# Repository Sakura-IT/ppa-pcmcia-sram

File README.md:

ppa-pcmcia-sram
===============

PCMCIA SRAM card created on ppa.pl forum.

* board - electrical schematics and board layout (Eagle, Gerber)
* cpld/src - CPLD core source (VHDL)
* docs - documentation (manual)

For history and rationale behind design decisions, See this thread: http://www.ppa.pl/forum/amiga/29264/budowa-kart-pamieci-sram-na-pcmcia

This board was sold and marketed as Sakura 4MB PCMCIA SRAM, primarily by Sakura IT, though several forks of this design exist.

Description
===========

Add 4MB of Fast RAM to your unexpanded Amiga 600/1200. This additional memory will make your system much faster and allow to run more demanding games and applications. It was designed by Jarosław Bieliński and Radosław Kujawa.

This memory expansion card has the following features:

* Adds 4MB of Fast RAM to Amiga 600 or Amiga 1200.
* Built using modern, high performance 55ns SRAM ICs (even faster than maximum Amiga 1200 slot access time).
* Accelerates unexpanded Amiga 1200 to at least 1.67 MIPS (according to SysInfo).
* Fully PCMCIA 2.1 compliant on an electrical level, smaller dimensions than normal PCMCIA card.
* Very simple installation - just insert the card into PCMCIA slot on the left side of Amiga.
* Compatible with all PCMCIA friendly accelerators and memory expansions.
* Open source design. 
* RoHS compliant, low power, environmentally friendly.
* Made by Amigans for Amigans!

We did our best to ensure that this card works on as many configurations as possible, but some accelerator and Fast RAM expansion designs are inherently incompatible with PCMCIA slot if more than 4MB of memory is installed. Note that PCMCIA SRAM should work with them anyway, if less than 4MB Fast was installed on the turbo card. Of course, if you don’t have any accelerator, you don’t have to worry about that.

The following A1200 cards are known to be PCMCIA compatible and should work correctly with any amount of memory installed:

* Blizzard 1230/1240/1260.
* Apollo 1240/1260.
* ACA 1220/1230/1231/1232.
* most other turbo cards supporting more than 8MB of Fast memory.
* 4MB Fast trapdoor expansions without CPU.

The following A1200 cards are known to be problematic if more than 4MB of memory is installed:

* Apollo/Elbox/Viper 1230LC.
* M-Tec 1230/28.
* Blizzard 1220 if more than 4MB RAM installed.
* 8MB Fast trapdoor expansions without CPU.

The following A600 cards are known to be PCMCIA compatible and should work correctly:

* ACA630.
* 4MB Fast expansions attached on top of processor.

The following A600 cards are known to be problematic if more than 4MB of memory is installed:

* ACA620 (in default PCMCIA-incompatible mode).
* Ninetails (in default PCMCIA-incompatible mode).
* 8MB/9.5MB Fast expansions attached on top of processor.

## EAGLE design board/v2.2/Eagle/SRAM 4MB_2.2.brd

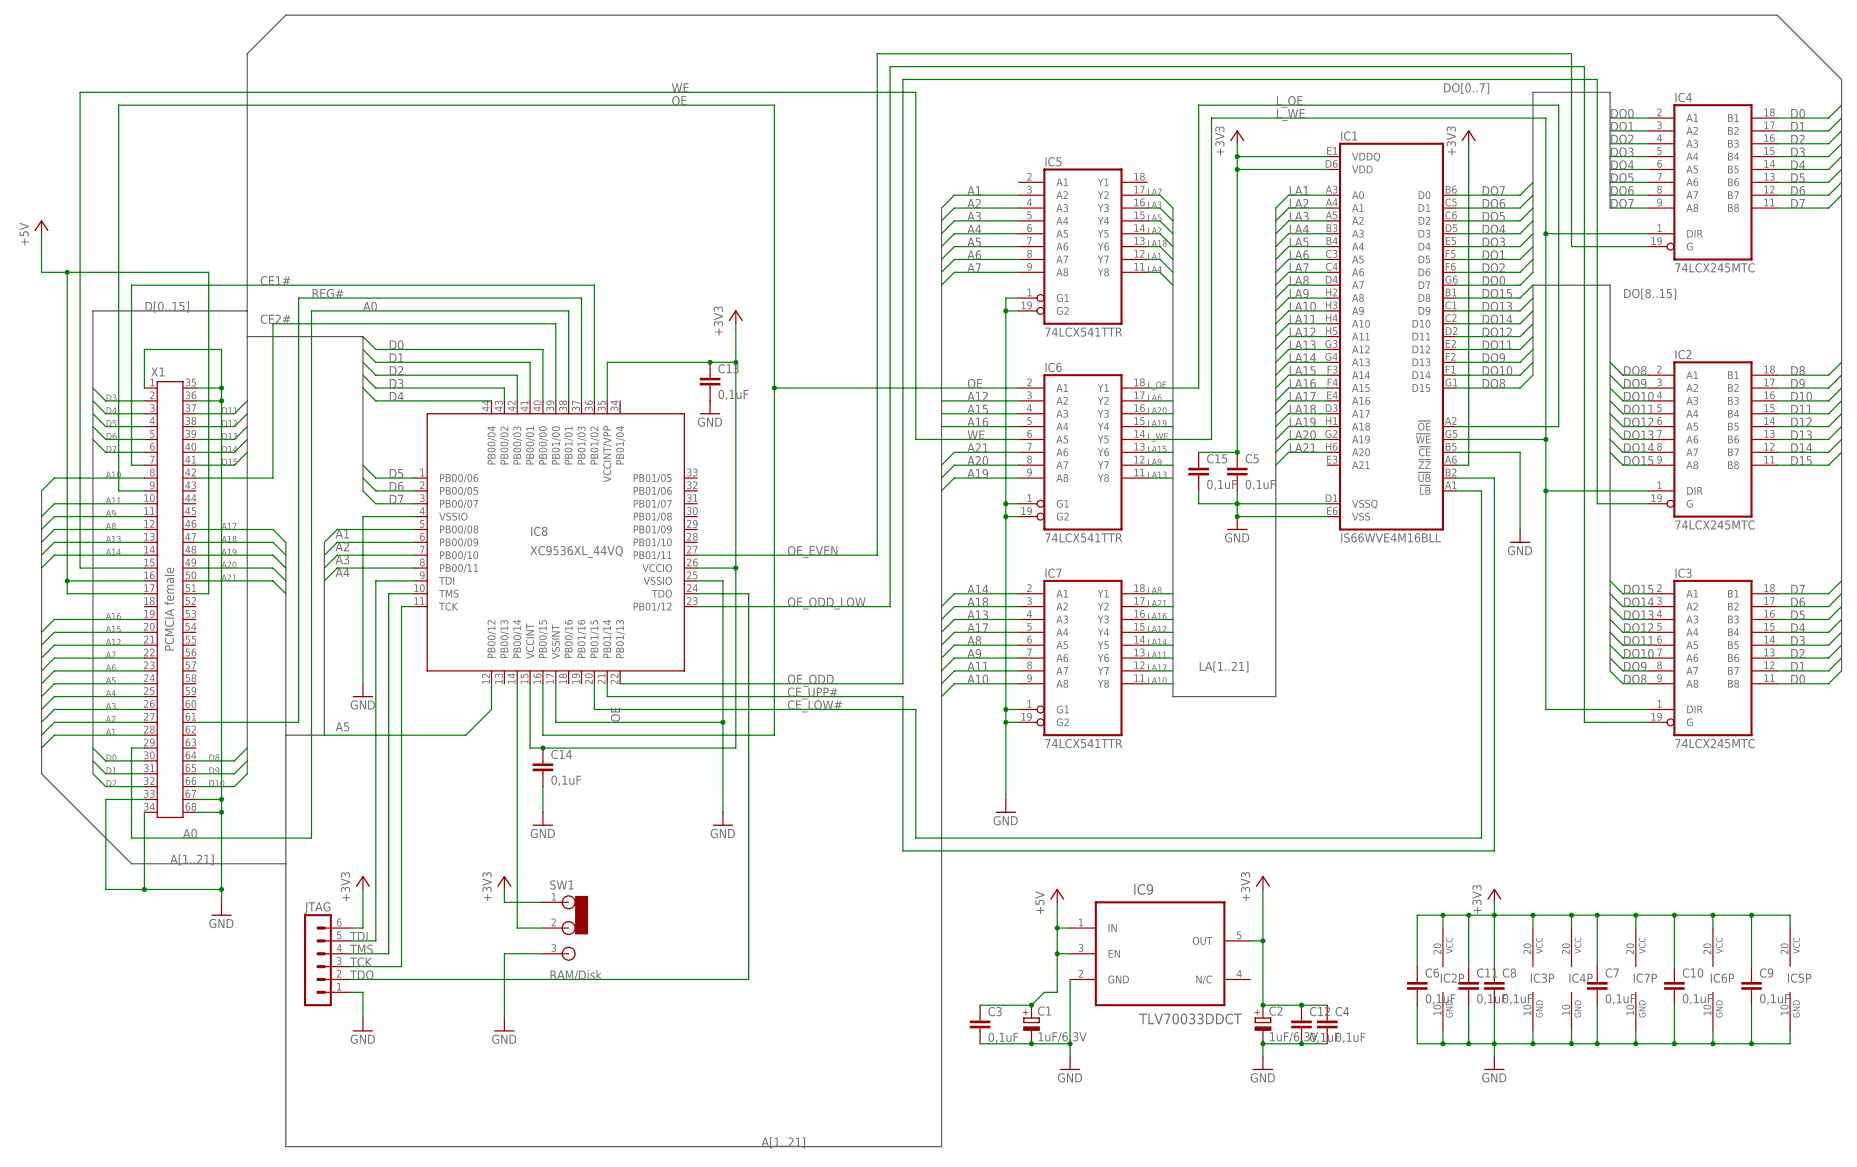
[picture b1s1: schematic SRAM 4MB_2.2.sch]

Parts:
C1, C2: 1uF/6,3V; A/3216-18R
C3, C4: 0,1uF; C0603
C5, C6, C7, C8, C9, C10, C11, C12, C13, C14, C15: 0,1uF; C0402K
IC1: IS66WVE4M16BLL; TFBGA48
IC2, IC3, IC4: 74LCX245MTC; TSSOP20
IC5, IC6, IC7: 74LCX541TTR; TSSOP20
IC8: XC9536XL_44VQ; SQFP-S-10X10-44
IC9: TLV70033DDCT; SOT95P280X110-5N
JTAG: MA06-1
SW1: RAM/Disk; SWITCH2
X1: PCMCIA female; 9M681X04

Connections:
+3V3: C2.+, C4.1, C5.1, C6.1, C7.1, C8.1, C9.1, C10.1, C11.1, C12.1, C13.1, C14.1, C15.1, IC1.A6 (!ZZ), IC1.D6 (VDD), IC1.E1 (VDDQ), IC2.20 (VCC), IC3.20 (VCC), IC4.20 (VCC), IC5.20 (VCC), IC6.20 (VCC), IC7.20 (VCC), IC8.15 (VCCINT), IC8.26 (VCCIO), IC8.35 (VCCINT/VPP), IC9.5 (OUT), JTAG.6, SW1.1
+5V: C1.+, C3.1, IC9.1 (IN), IC9.3 (EN), X1.16, X1.17, X1.51
A0: IC8.38 (PB01/01), X1.29
A1: IC5.3 (A2), IC8.5 (PB00/08), X1.28
A2: IC5.4 (A3), IC8.6 (PB00/09), X1.27
A3: IC5.5 (A4), IC8.7 (PB00/10), X1.26
A4: IC5.6 (A5), IC8.8 (PB00/11), X1.25
A5: IC5.7 (A6), IC8.12 (PB00/12), X1.24
A6: IC5.8 (A7), X1.23
A7: IC5.9 (A8), X1.22
A8: IC7.6 (A5), X1.12
A9: IC7.7 (A6), X1.11
A10: IC7.9 (A8), X1.8
A11: IC7.8 (A7), X1.10
A12: IC6.3 (A2), X1.21
A13: IC7.4 (A3), X1.13
A14: IC7.2 (A1), X1.14
A15: IC6.4 (A3), X1.20
A16: IC6.5 (A4), X1.19
A17: IC7.5 (A4), X1.46
A18: IC7.3 (A2), X1.47
A19: IC6.9 (A8), X1.48
A20: IC6.8 (A7), X1.49
A21: IC6.7 (A6), X1.50
CE1#: IC8.36 (PB01/02), X1.7
CE2#: IC8.39 (PB01/00), X1.42
CE_LOW#: IC1.A1 (!LB), IC8.20 (PB01/15)
CE_UPP#: IC1.B2 (!UB), IC8.21 (PB01/14)
D0: IC3.11 (B8), IC4.18 (B1), IC8.40 (PB00/00), X1.30
D1: IC3.12 (B7), IC4.17 (B2), IC8.41 (PB00/01), X1.31
D2: IC3.13 (B6), IC4.16 (B3), IC8.42 (PB00/03), X1.32
D3: IC3.14 (B5), IC4.15 (B4), IC8.43 (PB00/02), X1.2
D4: IC3.15 (B4), IC4.14 (B5), IC8.44 (PB00/04), X1.3
D5: IC3.16 (B3), IC4.13 (B6), IC8.1 (PB00/06), X1.4
D6: IC3.17 (B2), IC4.12 (B7), IC8.2 (PB00/05), X1.5
D7: IC3.18 (B1), IC4.11 (B8), IC8.3 (PB00/07), X1.6
D8: IC2.18 (B1), X1.64
D9: IC2.17 (B2), X1.65
D10: IC2.16 (B3), X1.66
D11: IC2.15 (B4), X1.37
D12: IC2.14 (B5), X1.38
D13: IC2.13 (B6), X1.39
D14: IC2.12 (B7), X1.40
D15: IC2.11 (B8), X1.41
DO0: IC1.G6 (D7), IC4.2 (A1)
DO1: IC1.F5 (D5), IC4.3 (A2)
DO2: IC1.F6 (D6), IC4.4 (A3)
DO3: IC1.E5 (D4), IC4.5 (A4)
DO4: IC1.D5 (D3), IC4.6 (A5)
DO5: IC1.C6 (D2), IC4.7 (A6)
DO6: IC1.C5 (D1), IC4.8 (A7)
DO7: IC1.B6 (D0), IC4.9 (A8)
DO8: IC1.G1 (D15), IC2.2 (A1), IC3.9 (A8)
DO9: IC1.F2 (D13), IC2.3 (A2), IC3.8 (A7)
DO10: IC1.F1 (D14), IC2.4 (A3), IC3.7 (A6)
DO11: IC1.E2 (D12), IC2.5 (A4), IC3.6 (A5)
DO12: IC1.D2 (D11), IC2.6 (A5), IC3.5 (A4)
DO13: IC1.C1 (D9), IC2.7 (A6), IC3.4 (A3)
DO14: IC1.C2 (D10), IC2.8 (A7), IC3.3 (A2)
DO15: IC1.B1 (D8), IC2.9 (A8), IC3.2 (A1)
GND: C1.-, C2.-, C3.2, C4.2, C5.2, C6.2, C7.2, C8.2, C9.2, C10.2, C11.2, C12.2, C13.2, C14.2, C15.2, IC1.B5 (!CE), IC1.D1 (VSSQ), IC1.E6 (VSS), IC2.10 (GND), IC3.10 (GND), IC4.10 (GND), IC5.1 (G1), IC5.10 (GND), IC5.19 (G2), IC6.1 (G1), IC6.10 (GND), IC6.19 (G2), IC7.1 (G1), IC7.10 (GND), IC7.19 (G2), IC8.4 (VSSIO), IC8.17 (VSSINT), IC8.25 (VSSIO), IC9.2 (GND), JTAG.1, SW1.3, X1.1, X1.33, X1.34, X1.35, X1.36, X1.67, X1.68
LA1: IC1.A3 (A0), IC5.12 (Y7)
LA2: IC1.A4 (A1), IC5.14 (Y5)
LA3: IC1.A5 (A2), IC5.16 (Y3)
LA4: IC1.B3 (A3), IC5.11 (Y8)
LA5: IC1.B4 (A4), IC5.15 (Y4)
LA6: IC1.C3 (A5), IC6.17 (Y2)
LA7: IC1.C4 (A6), IC5.17 (Y2)
LA8: IC1.D4 (A7), IC7.18 (Y1)
LA9: IC1.H2 (A8), IC6.12 (Y7)
LA10: IC1.H3 (A9), IC7.11 (Y8)
LA11: IC1.H4 (A10), IC7.13 (Y6)
LA12: IC1.H5 (A11), IC7.15 (Y4)
LA13: IC1.G3 (A12), IC6.11 (Y8)
LA14: IC1.G4 (A13), IC7.14 (Y5)
LA15: IC1.F3 (A14), IC6.13 (Y6)
LA16: IC1.F4 (A15), IC7.16 (Y3)
LA17: IC1.E4 (A16), IC7.12 (Y7)
LA18: IC1.D3 (A17), IC5.13 (Y6)
LA19: IC1.H1 (A18), IC6.15 (Y4)
LA20: IC1.G2 (A19), IC6.16 (Y3)
LA21: IC1.H6 (A20), IC7.17 (Y2)
L_OE: IC1.A2 (!OE), IC6.18 (Y1)
L_WE: IC1.G5 (!WE), IC2.1 (DIR), IC3.1 (DIR), IC4.1 (DIR), IC6.14 (Y5)
unnamed: IC8.14 (PB00/14), SW1.2
OE: IC6.2 (A1), IC8.16 (PB00/15), X1.9
OE_EVEN: IC4.19 (G), IC8.27 (PB01/11)
OE_ODD: IC2.19 (G), IC8.22 (PB01/13)
OE_ODD_LOW: IC3.19 (G), IC8.23 (PB01/12)
REG#: IC8.37 (PB01/03), X1.61
TCK: IC8.11 (TCK), JTAG.3
TDI: IC8.9 (TDI), JTAG.5
TDO: IC8.24 (TDO), JTAG.2
TMS: IC8.10 (TMS), JTAG.4
WE: IC6.6 (A5), X1.15

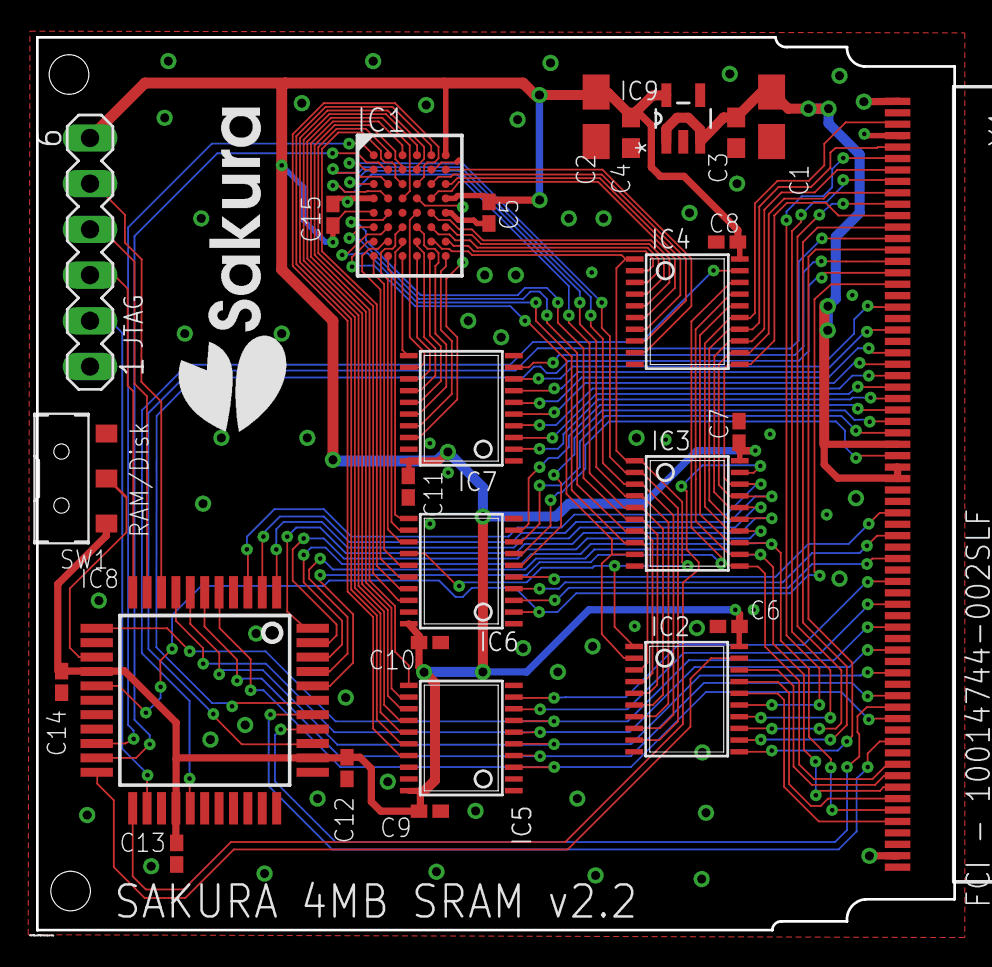
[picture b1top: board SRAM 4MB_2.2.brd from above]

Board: 2 copper layers, 51.0 x 49.6 mm, 27 parts (0 on the bottom side), 95 nets.

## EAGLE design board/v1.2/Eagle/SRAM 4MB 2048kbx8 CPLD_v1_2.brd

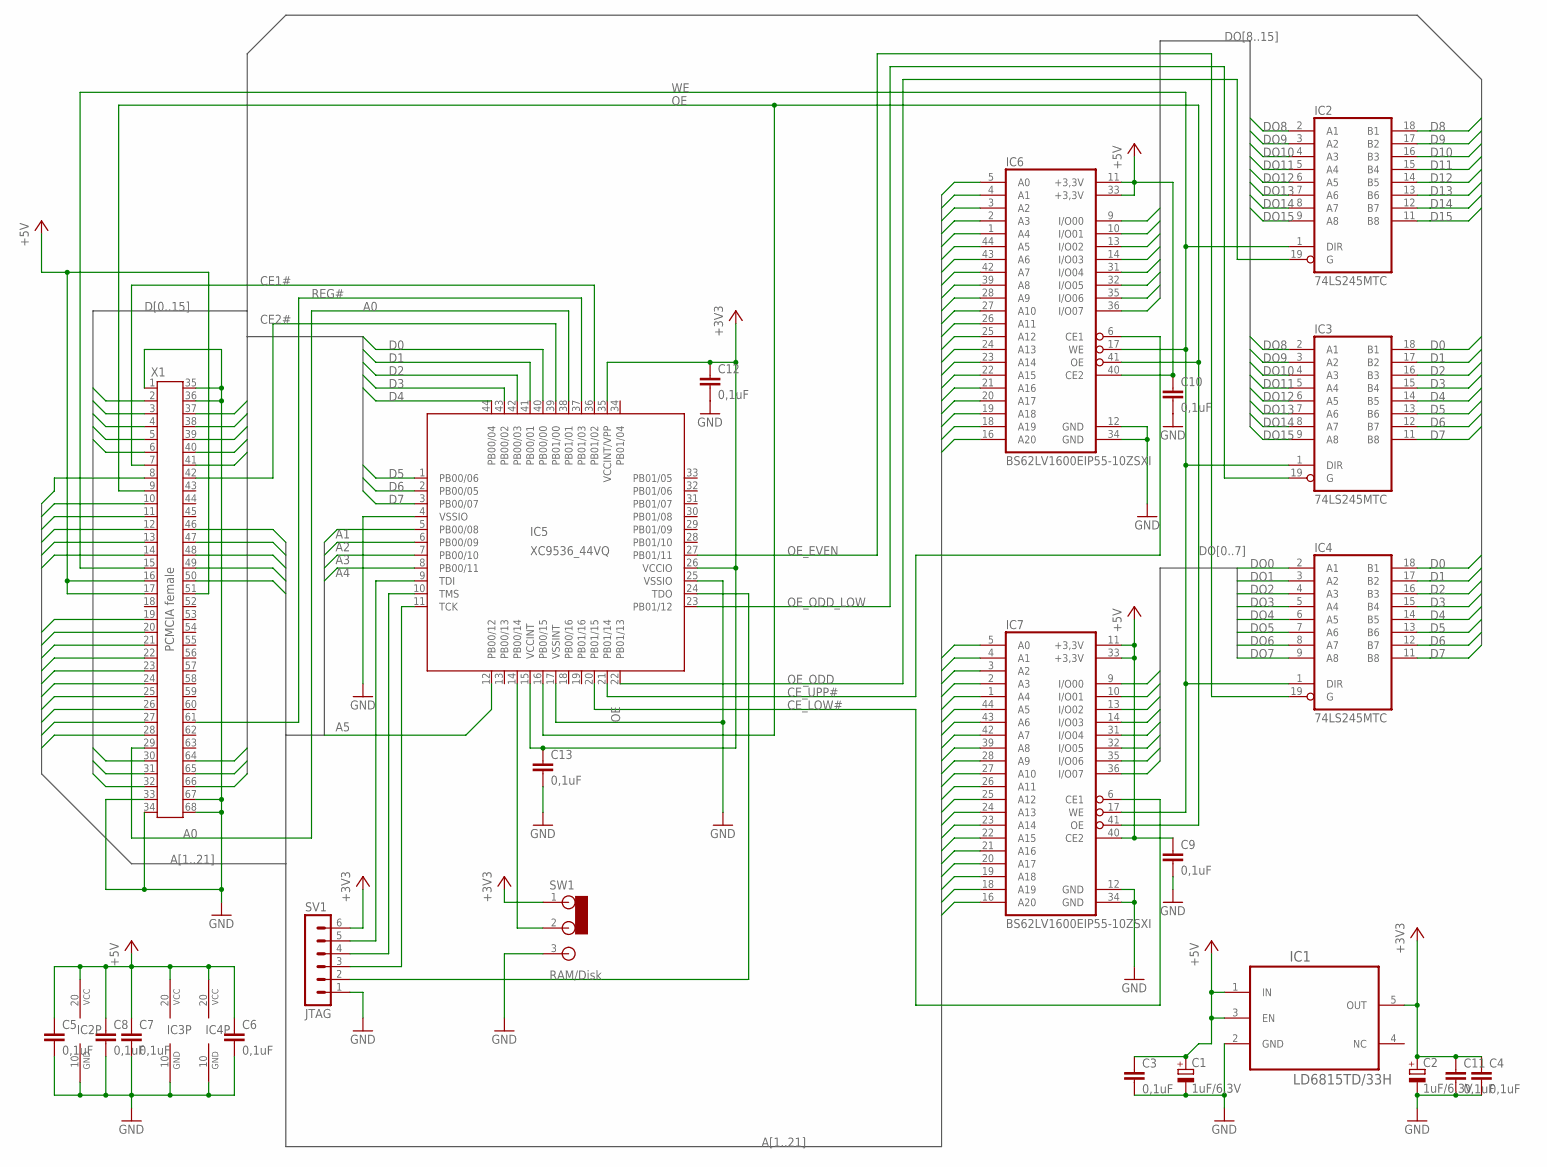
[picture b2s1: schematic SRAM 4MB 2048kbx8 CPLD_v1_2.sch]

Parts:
C1, C2: 1uF/6,3V; A/3216-18R
C3, C4, C5, C6, C7, C8, C9, C10, C11, C12, C13: 0,1uF; C0603
IC1: LD6815TD/33H; SOT95P275X110-5N
IC2, IC3, IC4: 74LS245MTC; TSSOP20
IC5: XC9536_44VQ; SQFP-S-10X10-44
IC6, IC7: BS62LV1600EIP55-10ZSXI; TSOPII-Z44
SV1: JTAG; MA06-1
SW1: RAM/Disk; SWITCH2
X1: PCMCIA female; 9M681X04

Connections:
+3V3: C2.+, C4.1, C11.1, C12.1, C13.1, IC1.5 (OUT), IC5.15 (VCCINT), IC5.26 (VCCIO), IC5.35 (VCCINT/VPP), SV1.6, SW1.1
+5V: C1.+, C3.1, C5.1, C6.1, C7.1, C8.1, C9.1, C10.1, IC1.1 (IN), IC1.3 (EN), IC2.20 (VCC), IC3.20 (VCC), IC4.20 (VCC), IC6.11 (+3,3V), IC6.33 (+3,3V), IC6.40 (CE2), IC7.11 (+3,3V), IC7.33 (+3,3V), IC7.40 (CE2), X1.16, X1.17, X1.51
A0: IC5.38 (PB01/01), X1.29
A1: IC5.5 (PB00/08), IC6.5 (A0), IC7.5 (A0), X1.28
A2: IC5.6 (PB00/09), IC6.4 (A1), IC7.4 (A1), X1.27
A3: IC5.7 (PB00/10), IC6.3 (A2), IC7.3 (A2), X1.26
A4: IC5.8 (PB00/11), IC6.2 (A3), IC7.2 (A3), X1.25
A5: IC5.12 (PB00/12), IC6.1 (A4), IC7.1 (A4), X1.24
A6: IC6.44 (A5), IC7.44 (A5), X1.23
A7: IC6.43 (A6), IC7.43 (A6), X1.22
A8: IC6.42 (A7), IC7.42 (A7), X1.12
A9: IC6.39 (A8), IC7.39 (A8), X1.11
A10: IC6.28 (A9), IC7.28 (A9), X1.8
A11: IC6.27 (A10), IC7.27 (A10), X1.10
A12: IC6.26 (A11), IC7.26 (A11), X1.21
A13: IC6.25 (A12), IC7.25 (A12), X1.13
A14: IC6.24 (A13), IC7.24 (A13), X1.14
A15: IC6.23 (A14), IC7.23 (A14), X1.20
A16: IC6.22 (A15), IC7.22 (A15), X1.19
A17: IC6.21 (A16), IC7.21 (A16), X1.46
A18: IC6.20 (A17), IC7.20 (A17), X1.47
A19: IC6.19 (A18), IC7.19 (A18), X1.48
A20: IC6.18 (A19), IC7.18 (A19), X1.49
A21: IC6.16 (A20), IC7.16 (A20), X1.50
CE1#: IC5.36 (PB01/02), X1.7
CE2#: IC5.39 (PB01/00), X1.42
CE_LOW#: IC5.20 (PB01/15), IC7.6 (CE1)
CE_UPP#: IC5.21 (PB01/14), IC6.6 (CE1)
D0: IC3.18 (B1), IC4.18 (B1), IC5.40 (PB00/00), X1.30
D1: IC3.17 (B2), IC4.17 (B2), IC5.41 (PB00/01), X1.31
D2: IC3.16 (B3), IC4.16 (B3), IC5.42 (PB00/03), X1.32
D3: IC3.15 (B4), IC4.15 (B4), IC5.43 (PB00/02), X1.2
D4: IC3.14 (B5), IC4.14 (B5), IC5.44 (PB00/04), X1.3
D5: IC3.13 (B6), IC4.13 (B6), IC5.1 (PB00/06), X1.4
D6: IC3.12 (B7), IC4.12 (B7), IC5.2 (PB00/05), X1.5
D7: IC3.11 (B8), IC4.11 (B8), IC5.3 (PB00/07), X1.6
D8: IC2.18 (B1), X1.64
D9: IC2.17 (B2), X1.65
D10: IC2.16 (B3), X1.66
D11: IC2.15 (B4), X1.37
D12: IC2.14 (B5), X1.38
D13: IC2.13 (B6), X1.39
D14: IC2.12 (B7), X1.40
D15: IC2.11 (B8), X1.41
DO0: IC4.2 (A1), IC7.9 (I/O00)
DO1: IC4.3 (A2), IC7.10 (I/O01)
DO2: IC4.4 (A3), IC7.13 (I/O02)
DO3: IC4.5 (A4), IC7.14 (I/O03)
DO4: IC4.6 (A5), IC7.31 (I/O04)
DO5: IC4.7 (A6), IC7.32 (I/O05)
DO6: IC4.8 (A7), IC7.35 (I/O06)
DO7: IC4.9 (A8), IC7.36 (I/O07)
DO8: IC2.2 (A1), IC3.2 (A1), IC6.9 (I/O00)
DO9: IC2.3 (A2), IC3.3 (A2), IC6.10 (I/O01)
DO10: IC2.4 (A3), IC3.4 (A3), IC6.13 (I/O02)
DO11: IC2.5 (A4), IC3.5 (A4), IC6.14 (I/O03)
DO12: IC2.6 (A5), IC3.6 (A5), IC6.31 (I/O04)
DO13: IC2.7 (A6), IC3.7 (A6), IC6.32 (I/O05)
DO14: IC2.8 (A7), IC3.8 (A7), IC6.35 (I/O06)
DO15: IC2.9 (A8), IC3.9 (A8), IC6.36 (I/O07)
GND: C1.-, C2.-, C3.2, C4.2, C5.2, C6.2, C7.2, C8.2, C9.2, C10.2, C11.2, C12.2, C13.2, IC1.2 (GND), IC2.10 (GND), IC3.10 (GND), IC4.10 (GND), IC5.4 (VSSIO), IC5.17 (VSSINT), IC5.25 (VSSIO), IC6.12 (GND), IC6.34 (GND), IC7.12 (GND), IC7.34 (GND), SV1.1, SW1.3, X1.1, X1.33, X1.34, X1.35, X1.36, X1.67, X1.68
unnamed: IC5.24 (TDO), SV1.2
unnamed: IC5.11 (TCK), SV1.3
unnamed: IC5.10 (TMS), SV1.4
unnamed: IC5.9 (TDI), SV1.5
unnamed: IC5.14 (PB00/14), SW1.2
OE: IC5.16 (PB00/15), IC6.41 (OE), IC7.41 (OE), X1.9
OE_EVEN: IC4.19 (G), IC5.27 (PB01/11)
OE_ODD: IC2.19 (G), IC5.22 (PB01/13)
OE_ODD_LOW: IC3.19 (G), IC5.23 (PB01/12)
REG#: IC5.37 (PB01/03), X1.61
WE: IC2.1 (DIR), IC3.1 (DIR), IC4.1 (DIR), IC6.17 (WE), IC7.17 (WE), X1.15

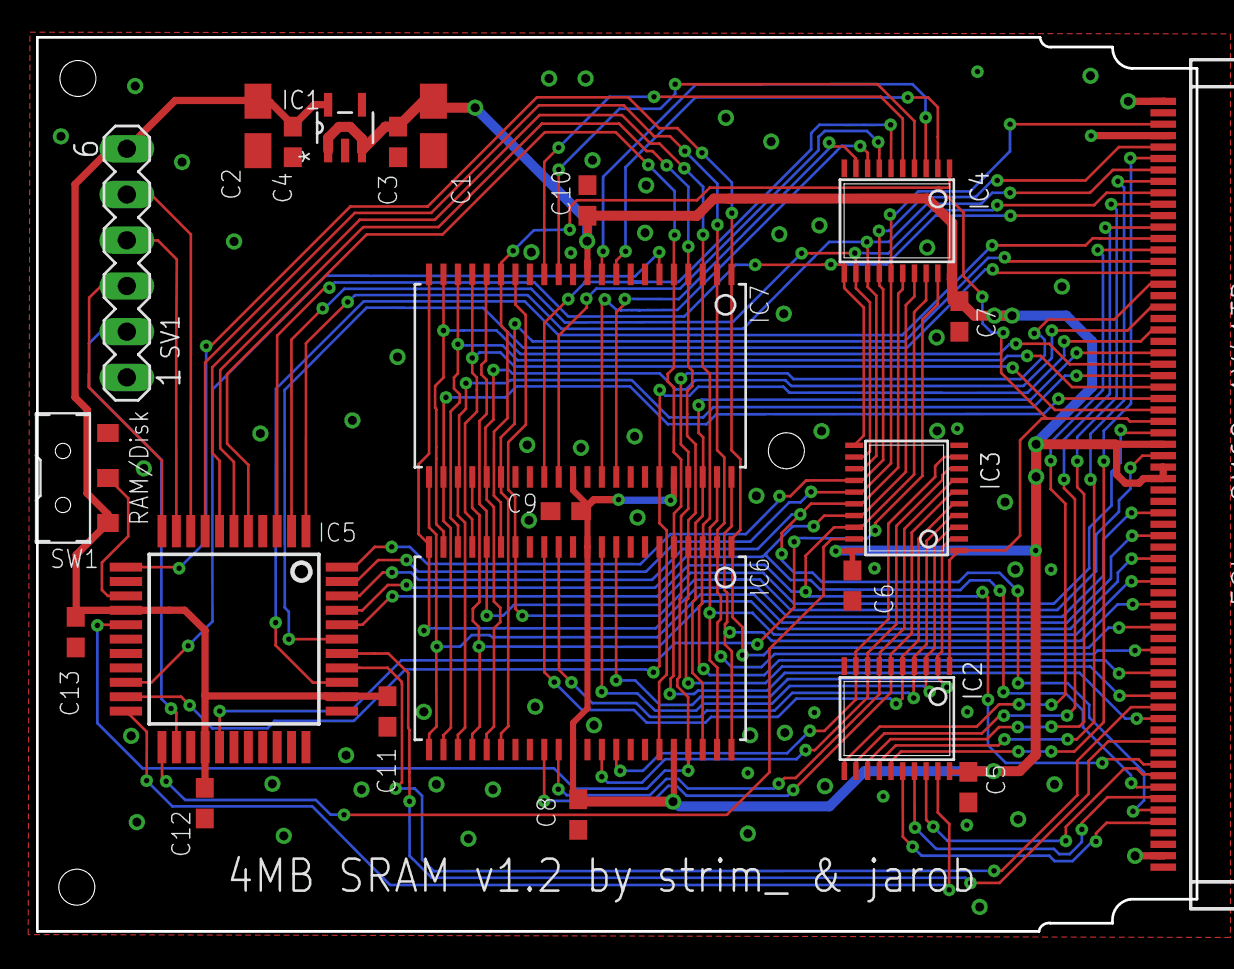
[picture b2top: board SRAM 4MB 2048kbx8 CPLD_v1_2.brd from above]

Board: 2 copper layers, 64.4 x 49.7 mm, 23 parts (0 on the bottom side), 72 nets.

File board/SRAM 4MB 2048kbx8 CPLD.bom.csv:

"Part";"Value";"Device";"Package";"Description";"MF";"MPN";"OC_FARNELL";"OC_NEWARK";"PACKAGE";"SUPPLIER";
"C1";"1uF/6,3V";"CPOL-EUB";"PANASONIC_B";"POLARIZED CAPACITOR, European symbol";"";"";"";"";"";"";
"C2";"1uF/6,3V";"CPOL-EUB";"PANASONIC_B";"POLARIZED CAPACITOR, European symbol";"";"";"";"";"";"";
"C3";"0,1uF";"C-EUC0603";"C0603";"CAPACITOR, European symbol";"";"";"";"";"";"";
"C4";"0,1uF";"C-EUC0603";"C0603";"CAPACITOR, European symbol";"";"";"";"";"";"";
"C5";"0,1uF";"C-EUC0603";"C0603";"CAPACITOR, European symbol";"";"";"";"";"";"";
"C6";"0,1uF";"C-EUC0603";"C0603";"CAPACITOR, European symbol";"";"";"";"";"";"";
"C7";"0,1uF";"C-EUC0603";"C0603";"CAPACITOR, European symbol";"";"";"";"";"";"";
"C9";"0,1uF";"C-EUC0603";"C0603";"CAPACITOR, European symbol";"";"";"";"";"";"";
"C10";"0,1uF";"C-EUC0603";"C0603";"CAPACITOR, European symbol";"";"";"";"";"";"";
"C11";"0,1uF";"C-EUC0603";"C0603";"CAPACITOR, European symbol";"";"";"";"";"";"";
"C12";"0,1uF";"C-EUC0603";"C0603";"CAPACITOR, European symbol";"";"";"";"";"";"";
"C13";"0,1uF";"C-EUC0603";"C0603";"CAPACITOR, European symbol";"";"";"";"";"";"";
"IC1";"M48Z02-70PC1";"M48Z02-70PC1";"DIP254P1524X965-24";"5 V, 16 Kbit (2 Kb x 8) ZEROPOWER® SRAM";"";"M48Z02-70PC1";"9755748";"89K1473";"PDIP-24";"STMICROELECTRONICS";
"IC2";"74LS245DW";"74LS245DW";"SO20W";"Octal BUS TRANSCEIVER, 3-state";"";"";"";"";"";"";
"IC3";"74LS245DW";"74LS245DW";"SO20W";"Octal BUS TRANSCEIVER, 3-state";"";"";"";"";"";"";
"IC4";"74LS245DW";"74LS245DW";"SO20W";"Octal BUS TRANSCEIVER, 3-state";"";"";"";"";"";"";
"IC5";"XC9536_44PLCC";"XC9536_44PLCC";"PLCC44";"xc9536_pc44 XC9500 In-System Programmable CPLD Family";"";"XC9536-15PCG44C";"1193226";"98K3376";"";"";
"IC6";"BS62LV1600EIP55-10ZSXI";"BS62LV1600EIP55-10ZSXI";"TSOPII-Z44";"Source: CYPRESS cy7c1059dv33_8.pdf";"";"";"";"";"";"";
"IC7";"BS62LV1600EIP55-10ZSXI";"BS62LV1600EIP55-10ZSXI";"TSOPII-Z44";"Source: CYPRESS cy7c1059dv33_8.pdf";"";"";"";"";"";"";
"IC8";"LD6815TD/33H";"LD6815TD/33H";"SOT95P275X110-5N";"LDO, 5.5V, 0.25VDO, 0.15A, 3.3V, 5TSOP";"";"LD6815TD/33H";"2308302";"69W9575";"TSOP-5";"NXP";
"SV1";"JTAG";"MA06-1";"MA06-1";"PIN HEADER";"";"";"unknown";"unknown";"";"";
"SV2";"";"MA06-1";"MA06-1";"PIN HEADER";"";"";"unknown";"unknown";"";"";
"SV3";"";"MA06-1";"MA06-1";"PIN HEADER";"";"";"unknown";"unknown";"";"";
"SV4";"RAM/DISK";"MA03-1";"MA03-1";"PIN HEADER";"";"";"unknown";"unknown";"";"";
"SV5";"ROM IN/OUT";"MA03-1";"MA03-1";"PIN HEADER";"";"";"unknown";"unknown";"";"";
"SV6";"";"MA08-1";"MA08-1";"PIN HEADER";"";"";"unknown";"unknown";"";"";
"SV7";"";"MA05-1";"MA05-1";"PIN HEADER";"";"";"unknown";"unknown";"";"";
"X1";"PCMCIA female";"9M681X03TB9M681Z04";"9M681X04";"";"";"";"";"";"";"";

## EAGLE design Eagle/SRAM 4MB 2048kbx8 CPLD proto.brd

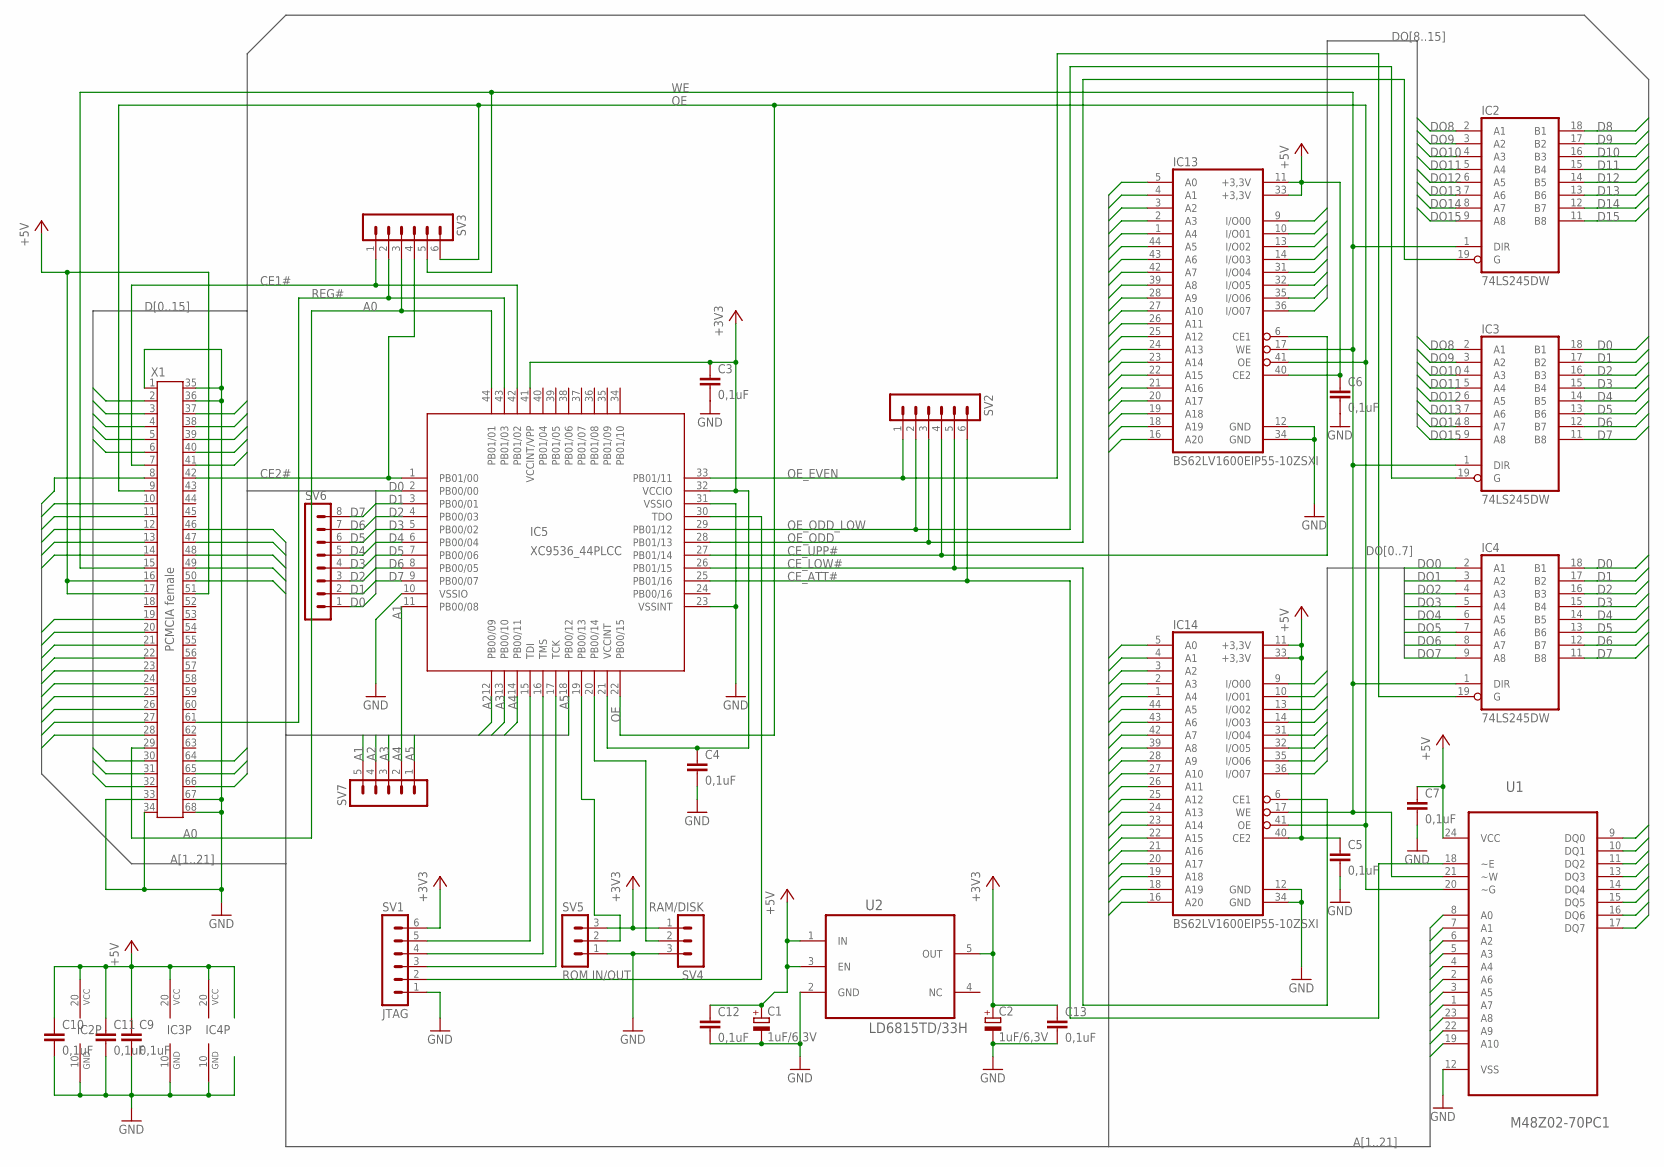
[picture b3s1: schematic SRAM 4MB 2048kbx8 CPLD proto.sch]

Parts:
C1, C2: 1uF/6,3V; PANASONIC_B
C3, C4, C5, C6, C7, C9, C10, C11, C12, C13: 0,1uF; C0603
IC2, IC3, IC4: 74LS245DW; SO20W
IC5: XC9536_44PLCC; PLCC44
IC13, IC14: BS62LV1600EIP55-10ZSXI; TSOPII-Z44
SV1: JTAG; MA06-1
SV2, SV3: MA06-1
SV4: RAM/DISK; MA03-1
SV5: ROM IN/OUT; MA03-1
SV6: MA08-1
SV7: MA05-1
U1: M48Z02-70PC1; DIP254P1524X965-24
U2: LD6815TD/33H; SOT95P275X110-5N
X1: PCMCIA female; 9M681X04

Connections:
+3V3: C2.+, C3.1, C4.1, C13.1, IC5.21 (VCCINT), IC5.32 (VCCIO), IC5.41 (VCCINT/VPP), SV1.6, SV4.1, SV5.3, U2.5 (OUT)
+5V: C1.+, C5.1, C6.1, C7.1, C9.1, C10.1, C11.1, C12.1, IC2.20 (VCC), IC3.20 (VCC), IC4.20 (VCC), IC13.11 (+3,3V), IC13.33 (+3,3V), IC13.40 (CE2), IC14.11 (+3,3V), IC14.33 (+3,3V), IC14.40 (CE2), U1.24 (VCC), U2.1 (IN), U2.3 (EN), X1.16, X1.17, X1.51
A0: IC5.44 (PB01/01), SV3.3, X1.29
A1: IC5.11 (PB00/08), IC13.5 (A0), IC14.5 (A0), SV7.5, U1.8 (A0), X1.28
A2: IC5.12 (PB00/09), IC13.4 (A1), IC14.4 (A1), SV7.4, U1.7 (A1), X1.27
A3: IC5.13 (PB00/10), IC13.3 (A2), IC14.3 (A2), SV7.3, U1.6 (A2), X1.26
A4: IC5.14 (PB00/11), IC13.2 (A3), IC14.2 (A3), SV7.2, U1.5 (A3), X1.25
A5: IC5.18 (PB00/12), IC13.1 (A4), IC14.1 (A4), SV7.1, U1.4 (A4), X1.24
A6: IC13.44 (A5), IC14.44 (A5), U1.2 (A6), X1.23
A7: IC13.43 (A6), IC14.43 (A6), U1.3 (A5), X1.22
A8: IC13.42 (A7), IC14.42 (A7), U1.1 (A7), X1.12
A9: IC13.39 (A8), IC14.39 (A8), U1.23 (A8), X1.11
A10: IC13.28 (A9), IC14.28 (A9), U1.22 (A9), X1.8
A11: IC13.27 (A10), IC14.27 (A10), U1.19 (A10), X1.10
A12: IC13.26 (A11), IC14.26 (A11), X1.21
A13: IC13.25 (A12), IC14.25 (A12), X1.13
A14: IC13.24 (A13), IC14.24 (A13), X1.14
A15: IC13.23 (A14), IC14.23 (A14), X1.20
A16: IC13.22 (A15), IC14.22 (A15), X1.19
A17: IC13.21 (A16), IC14.21 (A16), X1.46
A18: IC13.20 (A17), IC14.20 (A17), X1.47
A19: IC13.19 (A18), IC14.19 (A18), X1.48
A20: IC13.18 (A19), IC14.18 (A19), X1.49
A21: IC13.16 (A20), IC14.16 (A20), X1.50
CE1#: IC5.42 (PB01/02), SV3.1, X1.7
CE2#: IC5.1 (PB01/00), SV3.4, X1.42
CE_ATT#: IC5.25 (PB01/16), SV2.6, U1.18 (~E)
CE_LOW#: IC5.26 (PB01/15), IC14.6 (CE1), SV2.5
CE_UPP#: IC5.27 (PB01/14), IC13.6 (CE1), SV2.4
D0: IC3.18 (B1), IC4.18 (B1), IC5.2 (PB00/00), SV6.1, U1.9 (DQ0), X1.30
D1: IC3.17 (B2), IC4.17 (B2), IC5.3 (PB00/01), SV6.2, U1.10 (DQ1), X1.31
D2: IC3.16 (B3), IC4.16 (B3), IC5.4 (PB00/03), SV6.3, U1.11 (DQ2), X1.32
D3: IC3.15 (B4), IC4.15 (B4), IC5.5 (PB00/02), SV6.4, U1.13 (DQ3), X1.2
D4: IC3.14 (B5), IC4.14 (B5), IC5.6 (PB00/04), SV6.5, U1.14 (DQ4), X1.3
D5: IC3.13 (B6), IC4.13 (B6), IC5.7 (PB00/06), SV6.6, U1.15 (DQ5), X1.4
D6: IC3.12 (B7), IC4.12 (B7), IC5.8 (PB00/05), SV6.7, U1.16 (DQ6), X1.5
D7: IC3.11 (B8), IC4.11 (B8), IC5.9 (PB00/07), SV6.8, U1.17 (DQ7), X1.6
D8: IC2.18 (B1), X1.64
D9: IC2.17 (B2), X1.65
D10: IC2.16 (B3), X1.66
D11: IC2.15 (B4), X1.37
D12: IC2.14 (B5), X1.38
D13: IC2.13 (B6), X1.39
D14: IC2.12 (B7), X1.40
D15: IC2.11 (B8), X1.41
DO0: IC4.2 (A1), IC14.9 (I/O00)
DO1: IC4.3 (A2), IC14.10 (I/O01)
DO2: IC4.4 (A3), IC14.13 (I/O02)
DO3: IC4.5 (A4), IC14.14 (I/O03)
DO4: IC4.6 (A5), IC14.31 (I/O04)
DO5: IC4.7 (A6), IC14.32 (I/O05)
DO6: IC4.8 (A7), IC14.35 (I/O06)
DO7: IC4.9 (A8), IC14.36 (I/O07)
DO8: IC2.2 (A1), IC3.2 (A1), IC13.9 (I/O00)
DO9: IC2.3 (A2), IC3.3 (A2), IC13.10 (I/O01)
DO10: IC2.4 (A3), IC3.4 (A3), IC13.13 (I/O02)
DO11: IC2.5 (A4), IC3.5 (A4), IC13.14 (I/O03)
DO12: IC2.6 (A5), IC3.6 (A5), IC13.31 (I/O04)
DO13: IC2.7 (A6), IC3.7 (A6), IC13.32 (I/O05)
DO14: IC2.8 (A7), IC3.8 (A7), IC13.35 (I/O06)
DO15: IC2.9 (A8), IC3.9 (A8), IC13.36 (I/O07)
GND: C1.-, C2.-, C3.2, C4.2, C5.2, C6.2, C7.2, C9.2, C10.2, C11.2, C12.2, C13.2, IC2.10 (GND), IC3.10 (GND), IC4.10 (GND), IC5.10 (VSSIO), IC5.23 (VSSINT), IC5.31 (VSSIO), IC13.12 (GND), IC13.34 (GND), IC14.12 (GND), IC14.34 (GND), SV1.1, SV4.3, SV5.1, U1.12 (VSS), U2.2 (GND), X1.1, X1.33, X1.34, X1.35, X1.36, X1.67, X1.68
unnamed: IC5.30 (TDO), SV1.2
unnamed: IC5.17 (TCK), SV1.3
unnamed: IC5.16 (TMS), SV1.4
unnamed: IC5.15 (TDI), SV1.5
unnamed: IC5.19 (PB00/13), SV5.2
unnamed: IC5.20 (PB00/14), SV4.2
OE: IC5.22 (PB00/15), IC13.41 (OE), IC14.41 (OE), SV3.6, U1.20 (~G), X1.9
OE_EVEN: IC4.19 (G), IC5.33 (PB01/11), SV2.1
OE_ODD: IC2.19 (G), IC5.28 (PB01/13), SV2.3
OE_ODD_LOW: IC3.19 (G), IC5.29 (PB01/12), SV2.2
REG#: IC5.43 (PB01/03), SV3.2, X1.61
WE: IC2.1 (DIR), IC3.1 (DIR), IC4.1 (DIR), IC13.17 (WE), IC14.17 (WE), SV3.5, U1.21 (~W), X1.15

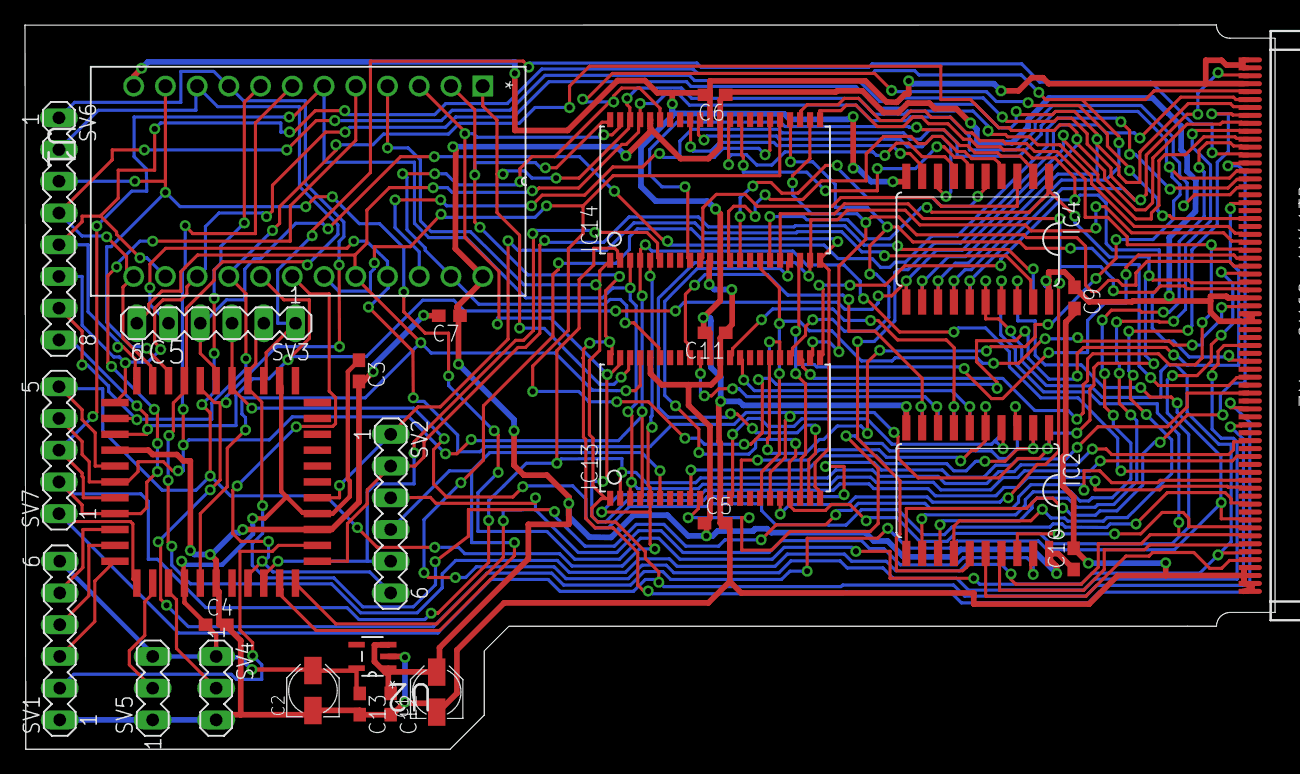
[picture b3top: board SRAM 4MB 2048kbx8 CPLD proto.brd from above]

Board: 2 copper layers, 100.1 x 58.0 mm, 28 parts (1 on the bottom side), 74 nets.

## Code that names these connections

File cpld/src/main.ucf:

# control signals from PCMCIA
NET "ce1" LOC = "42";
NET "ce2" LOC = "1";
NET "a0" LOC = "44"; # address bus bit 0
NET "reg" LOC = "43";
NET "oe_rom" LOC = "22";  # OE from PCMCIA in fact only used by ROM

# switches/jumpers
NET "sw_rom" LOC = "20";

# control signals to memory
NET "oe_even" LOC = "33";
NET "oe_oddlow" LOC = "29";
NET "oe_odd" LOC = "28";
NET "ce_upp" LOC = "27";
NET "ce_low" LOC = "26";
NET "ce_attr_external" LOC = "25";

# address bus (in fact A1-A5)
NET "addr<0>" LOC = "11";
NET "addr<1>" LOC = "12";
NET "addr<2>" LOC = "13";
NET "addr<3>" LOC = "14";
NET "addr<4>" LOC = "18";

# lowest 8 bits of data bus
NET "data<0>" LOC = "2";
NET "data<1>" LOC = "3";
NET "data<2>" LOC = "4";
NET "data<3>" LOC = "5";
NET "data<4>" LOC = "6";
NET "data<5>" LOC = "7";
NET "data<6>" LOC = "8";
NET "data<7>" LOC = "9";

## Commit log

2014-01-09 Import implementation as of 2013 jan 09.
2014-01-12 Put CIS tuples for RAM card into array. Simplify code.
2014-01-14 Better description
2014-01-14 Move my license to src
2014-02-14 Import latest schematics.
2014-03-06 Board in pdf, Eagle and gerber format
2014-03-07 New version of board
2014-03-11 Rearrange and clean up the repository contents.
2014-03-11 Update README to reflect the latest chaanges.
2014-03-13 PartList
2014-03-13 BOM file
2014-04-09 Add implementation constraints.
2014-05-09 New version board v1.2 on memory LY62W20488ML-55LL
    v1.2 on memory LY62W20488ML
    v2.0 on memory AS6C3216
2014-05-23 New version of board v2.1
2014-05-26 small change in the boards v2.1
2014-06-01 Add user's manual.
2014-06-02 Small change in the boards v2.0 and v2.1
2014-06-05 Minor updates to manual
    Rearrange stuff, add board layout image for v2.1.
2014-06-06 Ignore manual output files during commit.
2014-08-06 Add more information and FAQ to the user's manual.
2014-08-09 Add info about memory range.
2014-08-09 Complete CIS ROM in CPLD implementation.
    It is good enough for autodetection of SRAM as memory at 100ns. So far the
    RAM/disk switch just disables the CIS if set in "disk" position. Then the user
    can use PrepCard to write his own settings into beginning of common memory
    area. It needs further investigation if it makes sense to put "disk" CIS
    into CPLD (the filesystem has to be created anyway).
2014-08-09 CIS code is now integrated into main.vhd. Remove separate file.
2014-08-11 Add information about using the card as disk.
    While here note that files are licensed under CC BY-SA, with the
    exception of CPLD firmware which is under MIT.
2014-08-11 Add SRAM testing utility.
2014-08-22 Wording fixes in the manual.
2014-08-22 Move logo into separate directory
    Create common directory for files to be used by various documents.
2014-08-25 Add labels.
2014-08-28 Add sticker logo design.
2014-09-11 Minor changes to english manual.
    Change paper to A4, comment out info about lack of case, as our cards
    are delivered cased.
2014-09-11 Add Polish manual.
2014-09-11 .gitignore products of TeXing the manual
2014-11-17 Typos, wording, minor text corrections.
2014-11-17 Bring README up to date
2015-10-09 New board of PSRAM by ISSI
2015-10-10 New wersion board of PSRAM by ISSI
2018-12-21 Move description from website into repo.
    For archival purposes.
